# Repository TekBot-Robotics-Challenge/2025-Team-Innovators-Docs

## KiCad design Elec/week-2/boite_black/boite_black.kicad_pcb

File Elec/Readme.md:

# 📁 Documentation - Electronics Team

Welcome to the documentation folder of the **Electronics Team**. This repository centralizes all technical information related to circuit design, embedded programming, and integration of electronic systems for the TRC 2025 robot.

## 📌 Purpose

This folder aims to:  
- Document electrical architecture and circuit schematics  
- Centralize microcontroller programs and configurations  

## 📁 Folder Structure

📂 documentation-electronique/  
│  
├── 📁 fabrication/ → Production documentation  
│  
├── 📁 simulation/ → Component testing  
│  
└── 📁 realisation/ → Component assembly

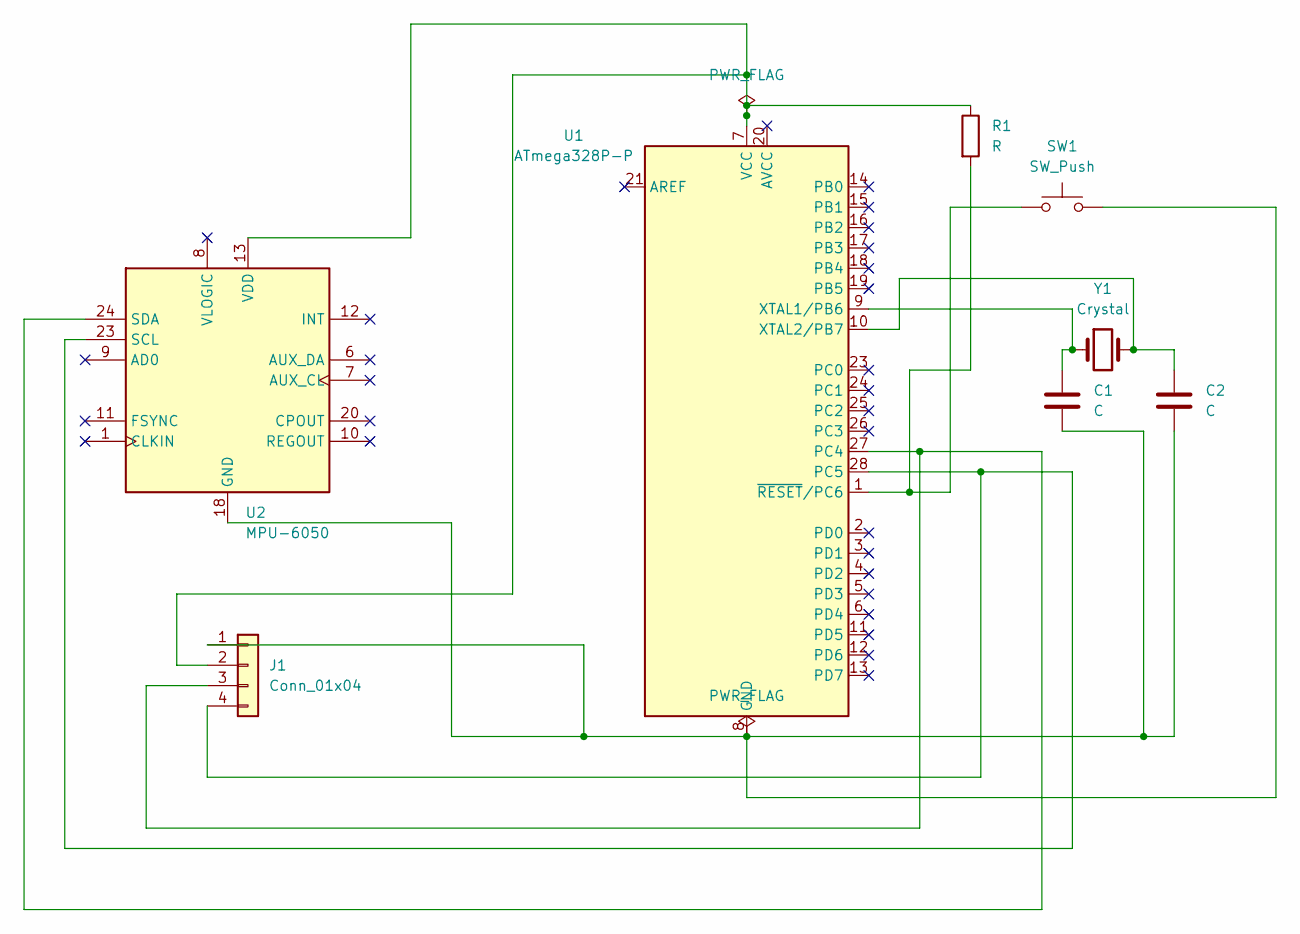
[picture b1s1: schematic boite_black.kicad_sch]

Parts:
C1, C2: C; C_Disc_D5.0mm_W2.5mm_P2.50mm
J1: Conn_01x04; PinHeader_1x04_P2.54mm_Vertical
R1: R; R_Axial_DIN0309_L9.0mm_D3.2mm_P12.70mm_Horizontal
SW1: SW_Push; SW_PUSH_6mm_H5mm
U1: ATmega328P-P; DIP-28_W7.62mm
U2: MPU-6050; InvenSense_QFN-24_4x4mm_P0.5mm
Y1: Crystal; Crystal_HC49-U_Vertical

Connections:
unnamed: C1.2, C2.2, J1.1, SW1.2, U1.8 (GND), U1.22 (GND), U2.18 (GND)
unnamed: J1.2, R1.1, U1.7 (VCC), U2.13 (VDD)
unnamed: J1.3, U1.27 (PC4), U2.24 (SDA)
unnamed: J1.4, U1.28 (PC5), U2.23 (SCL)
unnamed: C1.1, U1.9 (XTAL1/PB6), Y1.1
unnamed: C2.1, U1.10 (XTAL2/PB7), Y1.2
unnamed: R1.2, SW1.1, U1.1 (~RESET/PC6)

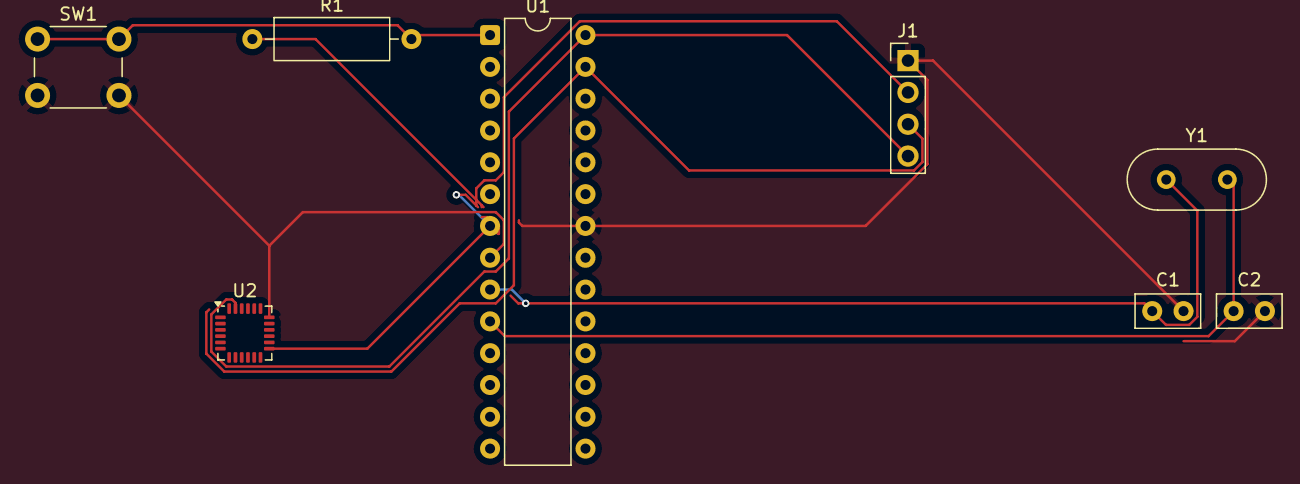
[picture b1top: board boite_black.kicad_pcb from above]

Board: 2 copper layers, 8 parts (0 on the bottom side), 7 nets.

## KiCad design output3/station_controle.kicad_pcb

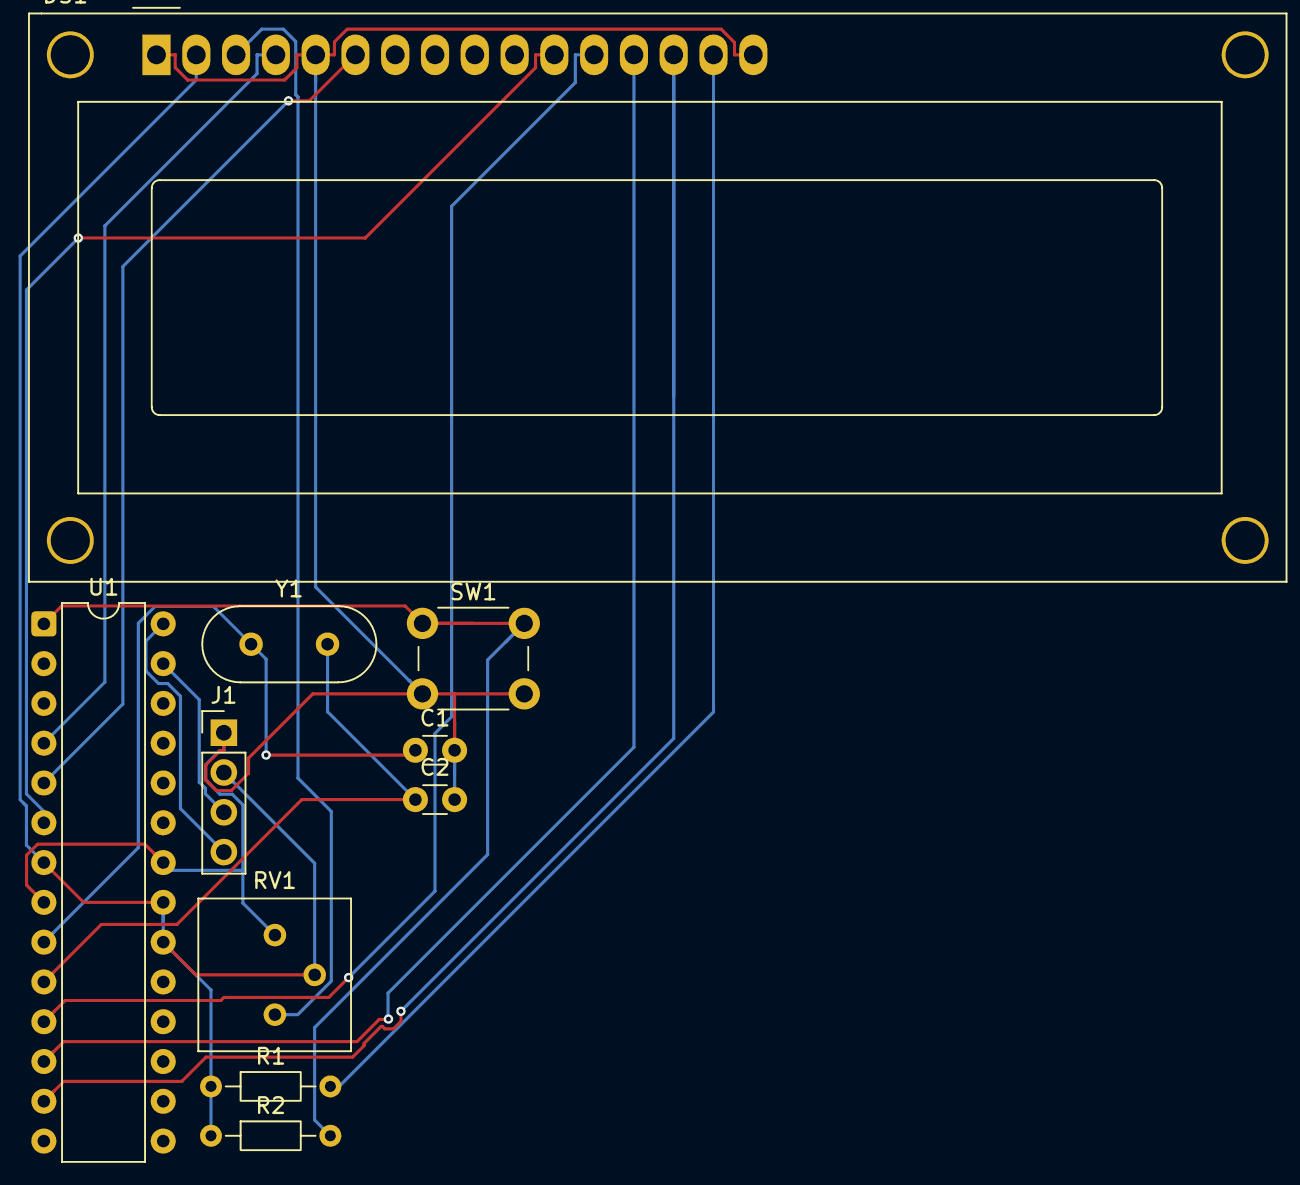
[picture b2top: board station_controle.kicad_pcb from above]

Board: 2 copper layers, 10 parts (0 on the bottom side), 15 nets.

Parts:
C1, C2: C; C_Disc_D3.0mm_W1.6mm_P2.50mm
DS1: WC1602A
J1: Conn_01x04; PinHeader_1x04_P2.54mm_Vertical
R1, R2: R; R_Axial_DIN0204_L3.6mm_D1.6mm_P7.62mm_Horizontal
RV1: R_Potentiometer; Potentiometer_Bourns_3386P_Vertical
SW1: SW_Push; SW_PUSH_6mm_H5mm
U1: ATmega328P-P; DIP-28_W7.62mm
Y1: Crystal; Crystal_HC49-U_Vertical

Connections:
unnamed: DS1.11 (D4), U1.6 (PD4)
unnamed: DS1.12 (D5), U1.11 (PD5)
unnamed: DS1.13 (D6), U1.12 (PD6)
unnamed: DS1.14 (D7), U1.13 (PD7)
unnamed: DS1.6 (E), U1.5 (PD3)
unnamed: DS1.15 (LED(+)), R1.2
unnamed: C1.2, C2.2, DS1.1 (VSS), DS1.5 (R/W), DS1.16 (LED(-)), J1.1, RV1.3, SW1.2, U1.8 (GND), U1.22 (GND)
unnamed: DS1.4 (RS), U1.4 (PD2)
unnamed: DS1.2 (VDD), J1.2, R1.1, R2.1, RV1.2, U1.7 (VCC), U1.20 (AVCC), U1.21 (AREF)
unnamed: DS1.3 (VO), RV1.1
unnamed: J1.3, U1.27 (PC4)
unnamed: J1.4, U1.28 (PC5)
unnamed: C1.1, U1.9 (XTAL1/PB6), Y1.1
unnamed: C2.1, U1.10 (XTAL2/PB7), Y1.2
unnamed: R2.2, SW1.1, U1.1 (~RESET/PC6)

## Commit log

2025-06-10 initialisation architecture
2025-06-10 website
2025-06-11 Création de la classe Robot+Encapsulation+héritage
2025-06-11 feat/Modification de la méthode travailler de la classe RobotDomestique et import global de Random
2025-06-12 doc meca
2025-06-12 Ajout de la section simulation vidéo et du fichier preview GIF
2025-06-12 add assemblage
2025-06-12 Corrige les liens et l’affichage des images dans le guide Elec pour GitHub
2025-06-12 doc update
2025-06-12 piece4
2025-06-12 ajout de readme_UML.md
2025-06-13 deploiement
2025-06-13 Ajout des fichiers de build à la racine pour GitHub Pages
2025-06-13 Déploiement GitHub Pages React Vite
2025-06-13 Déploiement GitHub final
2025-06-14 Nouvelle approche pour le déploiement
2025-06-14 Deploy Vite site to GitHub Pages
2025-06-15 Test-2: Introduction à ROS
2025-06-16 Restructuration du siteweb
2025-06-16 part 1 a & b
2025-06-16 Ajout de la documentation de IT et Electronique dans le site
2025-06-16 Mise à jour du titre de la section du sidebar
2025-06-17 doc semaine 2
2025-06-17 semaine 1 mécanique
2025-06-18 Sauvegarde des fichiers locaux avant merge
2025-06-18 modification de la partie mécanique
2025-06-18 Modification du fichier mecanique semaine1
2025-06-18 emoji to lucid-react icon
2025-06-18 modification du lien en téléchargement
2025-06-19 lien du fichier output
2025-06-19 suppression du fichier output dans /pages/Mecanique
2025-06-19 modification du lien du dossier output en lien absolu
2025-06-19 modification du téléchargement des fichiers
2025-06-19 Ajout des fonctionnalités terminées
2025-06-19 documentation semaine 2
2025-06-20 Rendre fichier telechargeable
2025-06-23 IT week-3
2025-06-23 mise à jour doc IT
2025-06-23 mise à jour documentation IT
2025-06-26 meca test 3
2025-06-27 Mise à jour doc
2025-06-28 Restructure and document mechanical test files
    Moved and renamed part files, screenshots, and mass reports for better organization. Added detailed documentation for the advanced mechanical test, including objectives, modeling steps, and configura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
2025-06-28 Remove Test 3 assets and related files
    Deleted all images, CAD files, PDFs, and step images from the Test 3 directory, including subfolders A, B, C, and Steps. This cleanup likely reflects the removal or deprecation of Test 3 and its asso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
2025-06-28 modification test3 IT
2025-06-28 Implémentation de la documentation semaine 3 pour le pole Mécanique
2025-06-28 resolution de styleCSS dans mecanique.tsx
2025-06-28 challenge2
2025-06-28 ajout semaine 3
2025-06-28 Semaine 2 et 3 de l'équipe Elec
2025-06-28 Ajout des fichiers telechargeable pour la semaine3 de elec
2025-07-04 Update doc
2025-07-09 site web du test final
2025-07-09 site web test final
2025-07-09 testmecafinal initdoc
2025-07-10 test farany elec
2025-07-13 update siteweb
2025-07-20 Update documentation and add CAD models and screenshots
    Revised the mechanical design documentation to reflect changes in materials and construction, including the use of laser-cut wood and PVC for the conveyor. Added SolidWorks assembly and part files fo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
2025-07-24 Update test final Meca
2025-07-24 add vite
2025-07-24 resolve build
2025-07-24 fichier telechargeable
2025-07-25 fichier telechargeable meca test final
2025-07-25 fix: fichier telechargeable meca test final
2025-07-25 ajout de Aile_droite.SLDPRT dans outputTestFinal
2025-07-28 implémentation video capteur objet et couleur
2025-07-28 message
2025-09-10 description generale
2026-01-05 page final
2026-01-05 Final
